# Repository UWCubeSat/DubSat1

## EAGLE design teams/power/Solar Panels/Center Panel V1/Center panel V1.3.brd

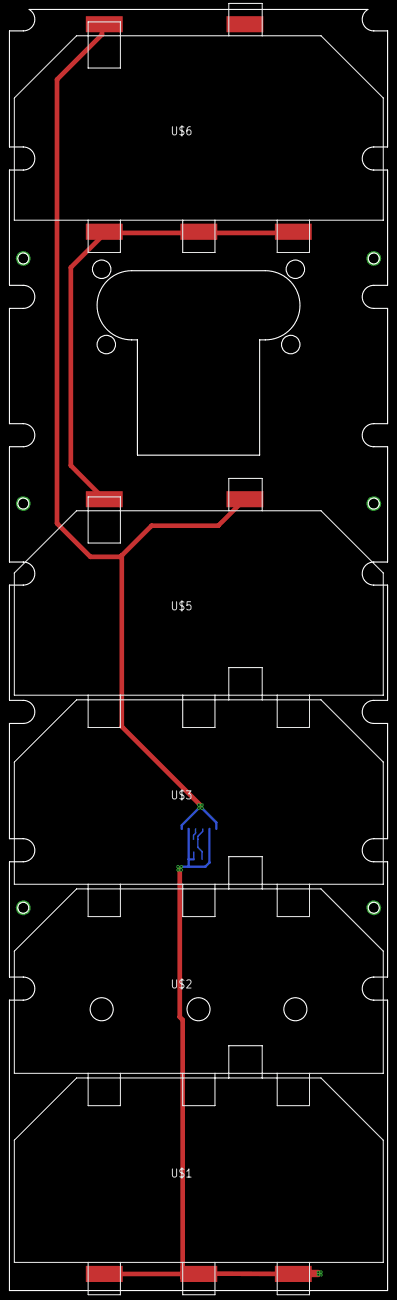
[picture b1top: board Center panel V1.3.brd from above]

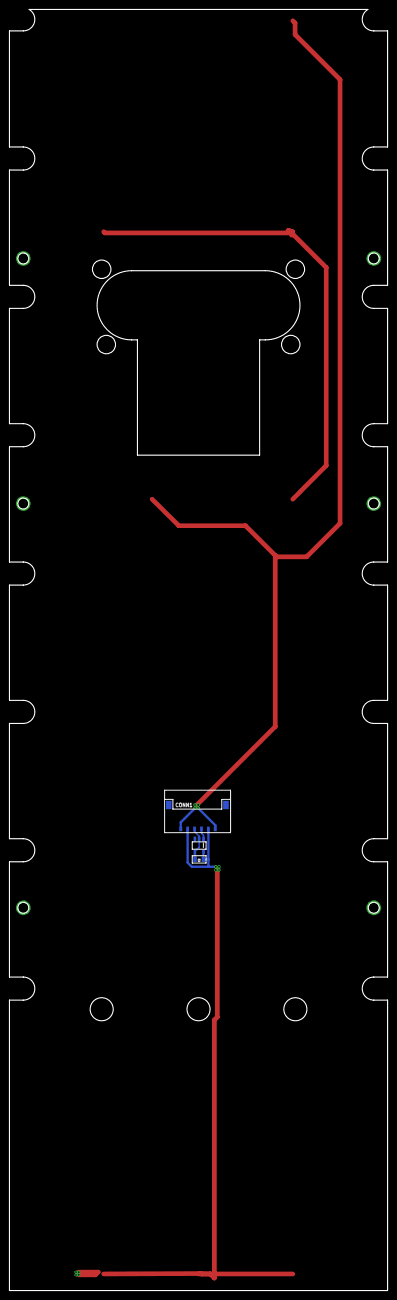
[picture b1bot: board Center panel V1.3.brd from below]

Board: 2 copper layers, 82.0 x 277.8 mm, 8 parts (3 on the bottom side), 5 nets.

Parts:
C2: 0805
CONN1: PICOLOCK_6
U$1: SOLAR_CELL_BOTTOM; SOLAR_CELL_BOTTOM_SHORT-PADS
U$2, U$3: SOALAR_CELL_OUTLINE; SOLAR_CELL_OUTLINE
U$5: SOLAR_CELL_TOP; SOLAR_CELL_TOP_SHORT-PAD
U$6: SOLAR_CELL_STAND-ALONE
U$7: TMP36; SOT-23-5

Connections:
3V3: C2.1, CONN1.P$3, U$7.P$2, U$7.P$4
GND: CONN1.P$2, CONN1.P$5, U$1.P$1, U$1.P$2, U$1.P$3, U$7.P$5
unnamed: U$5.P$2, U$6.P$1, U$6.P$2, U$6.P$3
POWER: CONN1.P$1, CONN1.P$6, U$5.P$1, U$6.P$5
VOUT: CONN1.P$4, U$7.P$1

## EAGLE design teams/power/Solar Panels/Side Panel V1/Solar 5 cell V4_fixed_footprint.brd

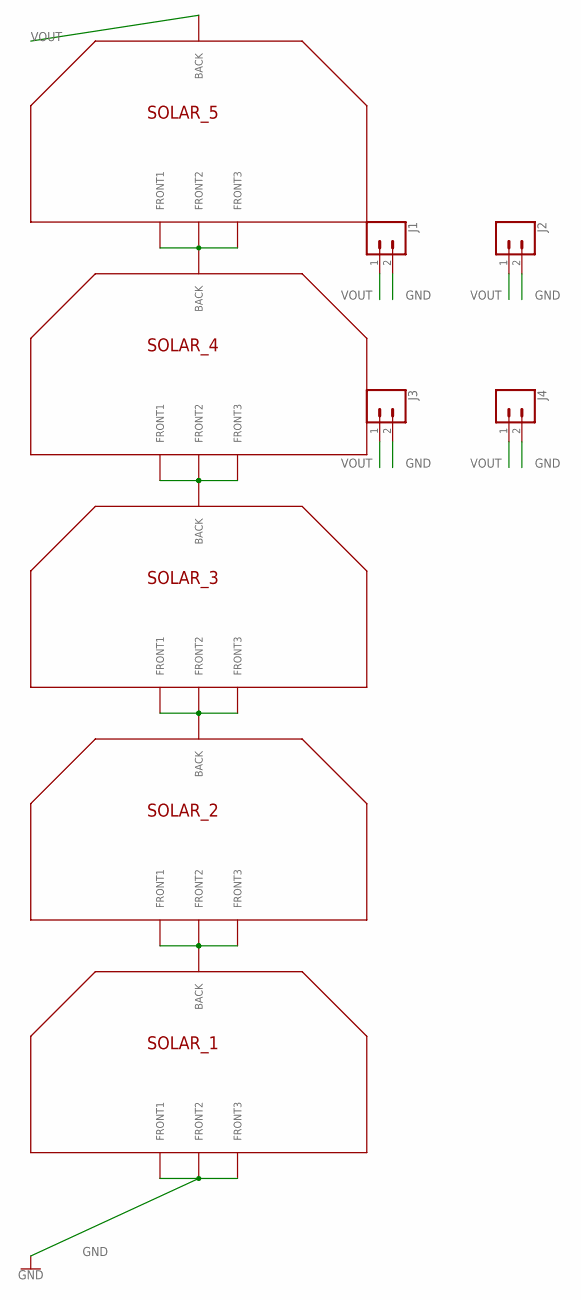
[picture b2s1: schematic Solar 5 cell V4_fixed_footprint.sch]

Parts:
J1, J2, J3, J4: CONN_02; 1X02
SOLAR_1, SOLAR_2, SOLAR_3, SOLAR_4, SOLAR_5: SOLAR_CELL_HALF_TABSFULL_TABS; SOLAR_CELL_3G30A_FULL_TABS

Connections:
1-2: SOLAR_1.P$1 (BACK), SOLAR_2.P$F1 (FRONT1), SOLAR_2.P$F2 (FRONT2), SOLAR_2.P$F3 (FRONT3)
2-3: SOLAR_2.P$1 (BACK), SOLAR_3.P$F1 (FRONT1), SOLAR_3.P$F2 (FRONT2), SOLAR_3.P$F3 (FRONT3)
3-4: SOLAR_3.P$1 (BACK), SOLAR_4.P$F1 (FRONT1), SOLAR_4.P$F2 (FRONT2), SOLAR_4.P$F3 (FRONT3)
4-5: SOLAR_4.P$1 (BACK), SOLAR_5.P$F1 (FRONT1), SOLAR_5.P$F2 (FRONT2), SOLAR_5.P$F3 (FRONT3)
GND: J1.2, J2.2, J3.2, J4.2, SOLAR_1.P$F1 (FRONT1), SOLAR_1.P$F2 (FRONT2), SOLAR_1.P$F3 (FRONT3)
VOUT: J1.1, J2.1, J3.1, J4.1, SOLAR_5.P$1 (BACK)

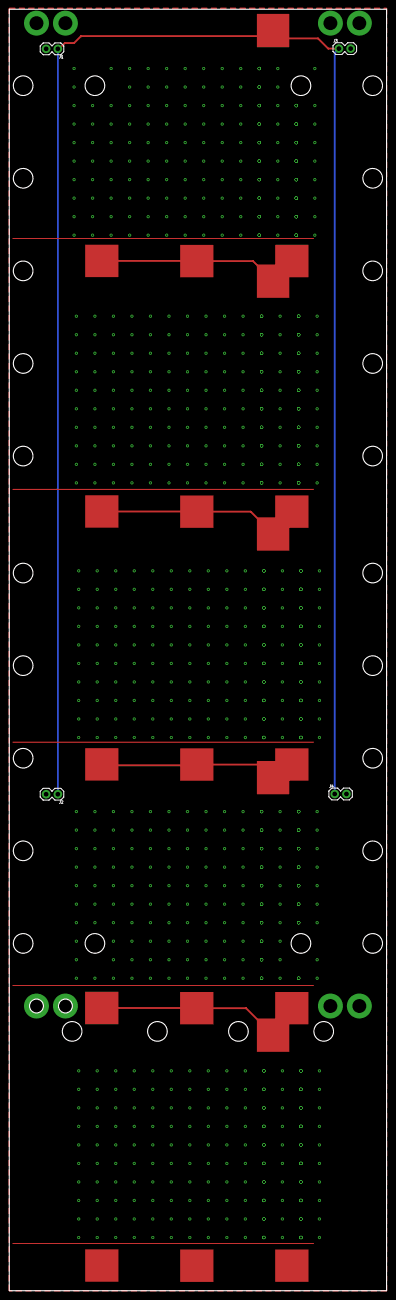
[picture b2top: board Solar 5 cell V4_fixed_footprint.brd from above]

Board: 2 copper layers, 81.5 x 276.8 mm, 9 parts (0 on the bottom side), 6 nets.

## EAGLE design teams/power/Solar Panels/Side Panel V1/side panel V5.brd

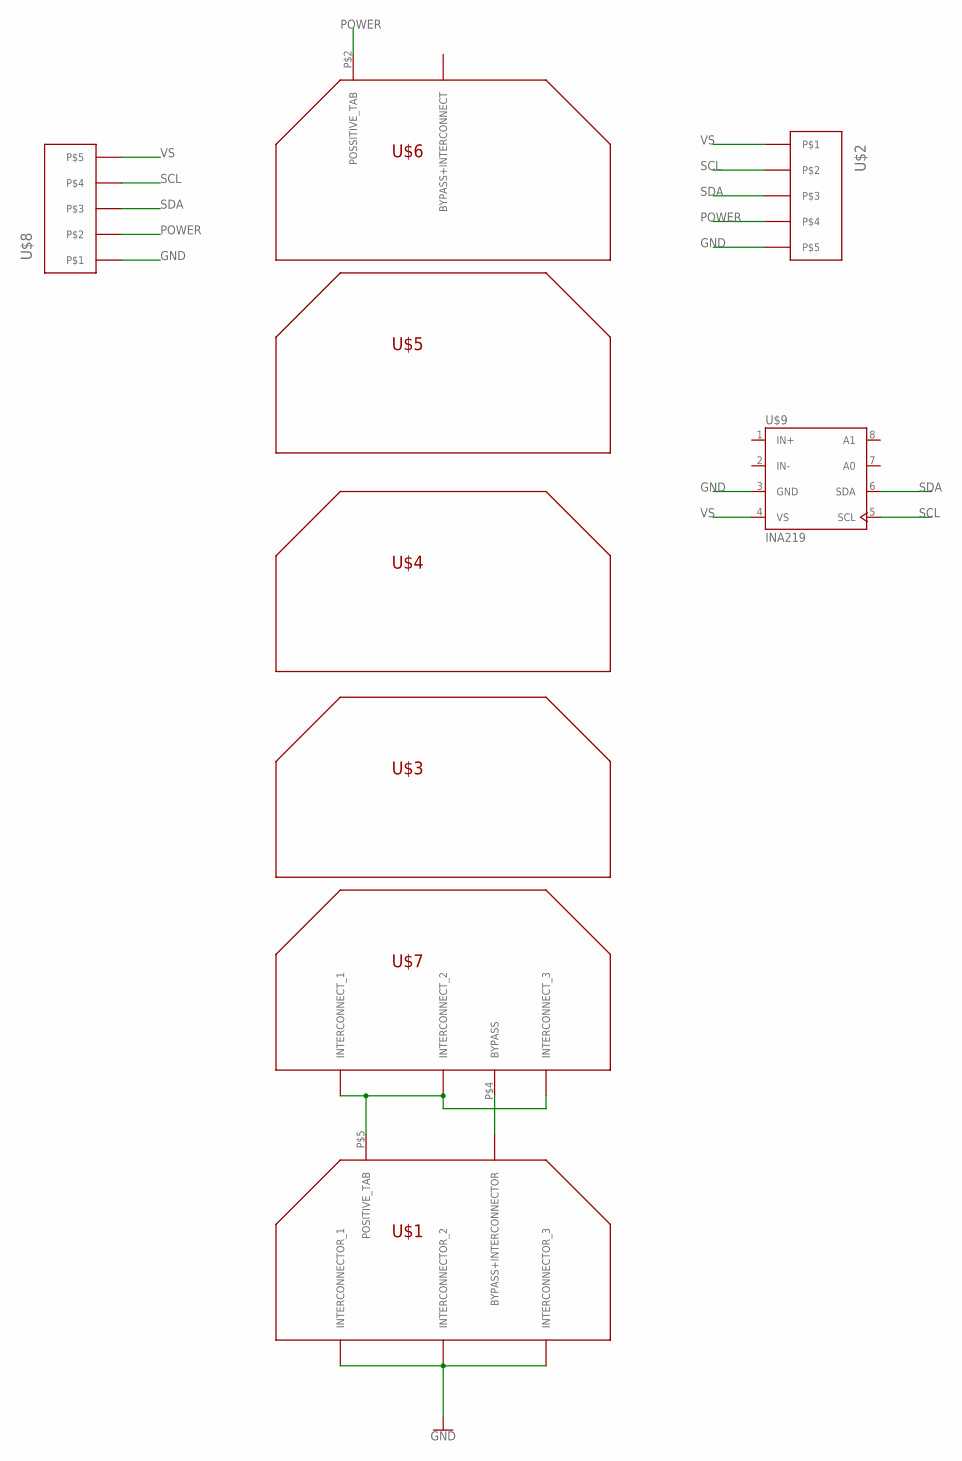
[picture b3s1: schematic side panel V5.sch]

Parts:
U$1: SOLAR_CELL_STAND-ALONE
U$2, U$8: PICOLOCK_5
U$3, U$4, U$5: SOALAR_CELL_OUTLINE; SOLAR_CELL_OUTLINE
U$6: SOLAR_CELL_TOP; SOLAR_CELL_TOP_SHORT-PAD
U$7: SOLAR_CELL_BOTTOM+BYPASS
U$9: INA219; S008

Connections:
GND: U$1.P$1 (INTERCONNECTOR_1), U$1.P$2 (INTERCONNECTOR_2), U$1.P$3 (INTERCONNECTOR_3), U$2.P$5, U$8.P$1, U$9.3 (GND)
unnamed: U$1.P$4 (BYPASS+INTERCONNECTOR), U$7.P$4 (BYPASS)
unnamed: U$1.P$5 (POSITIVE_TAB), U$7.P$1 (INTERCONNECT_1), U$7.P$2 (INTERCONNECT_2), U$7.P$3 (INTERCONNECT_3)
POWER: U$2.P$4, U$6.P$2 (POSSITIVE_TAB), U$8.P$2
SCL: U$2.P$2, U$8.P$4, U$9.5 (SCL)
SDA: U$2.P$3, U$8.P$3, U$9.6 (SDA)
VS: U$2.P$1, U$8.P$5, U$9.4 (VS)

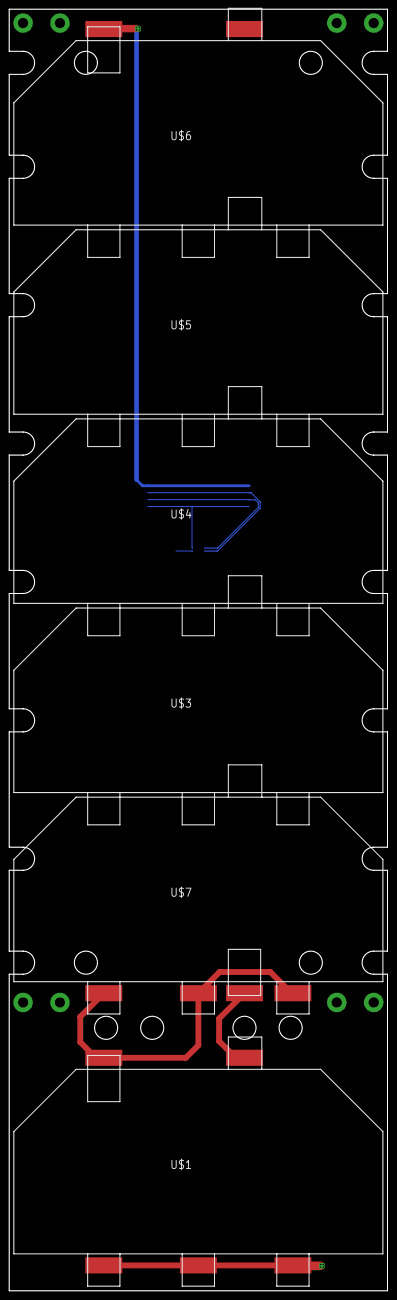
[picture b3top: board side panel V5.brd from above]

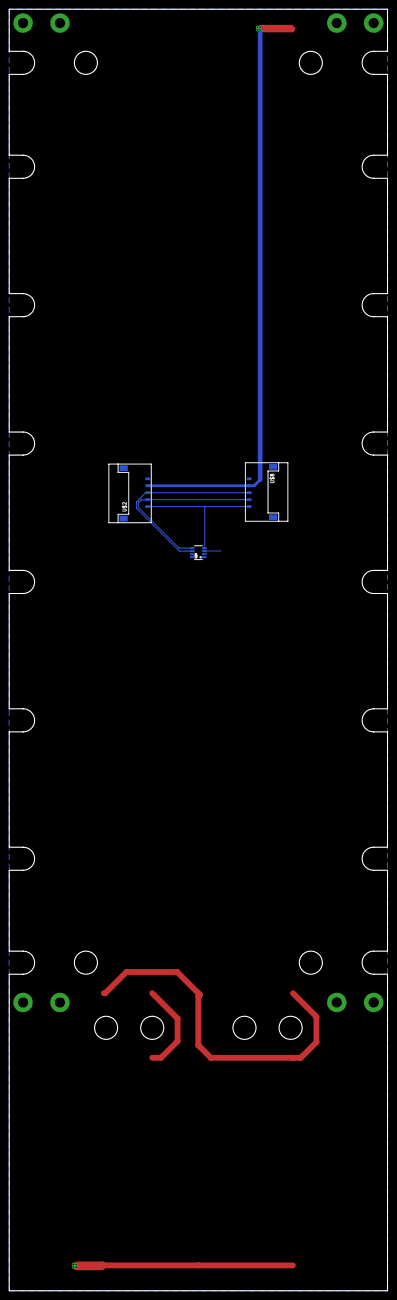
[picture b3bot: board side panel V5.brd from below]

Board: 2 copper layers, 82.0 x 277.8 mm, 9 parts (3 on the bottom side), 7 nets.

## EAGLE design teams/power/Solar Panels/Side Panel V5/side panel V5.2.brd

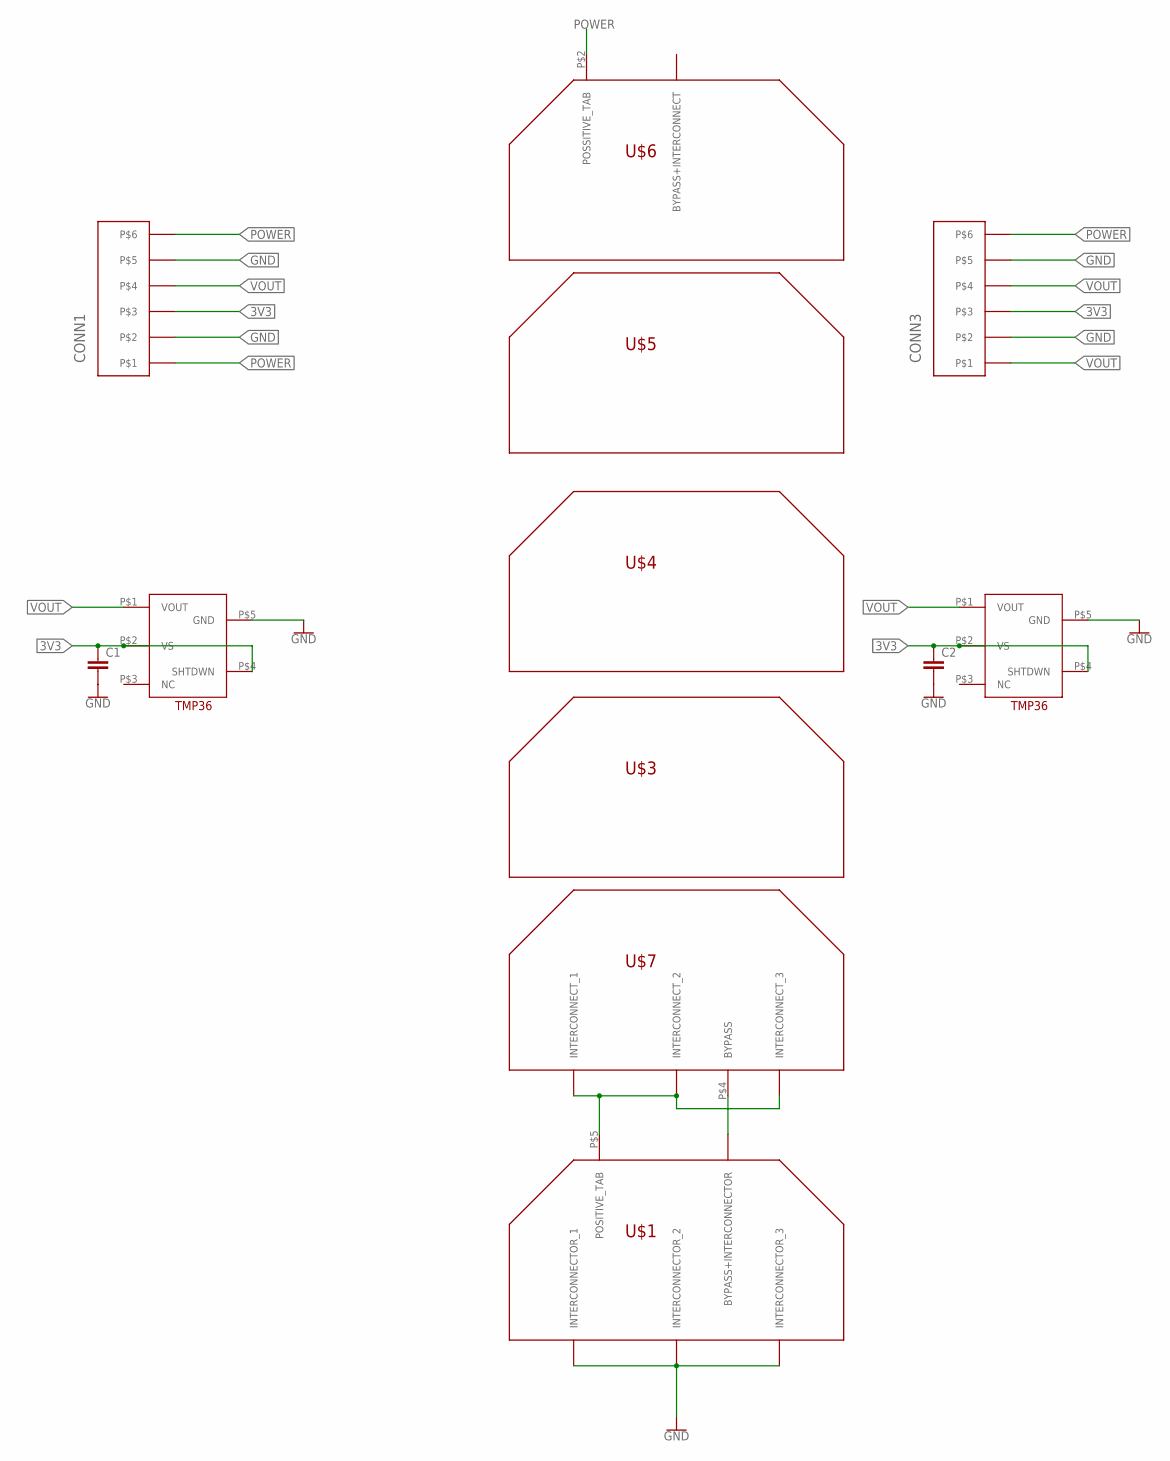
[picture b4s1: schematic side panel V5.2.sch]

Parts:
C1, C2: CAPACITOR0805; 0805
CONN1, CONN3: PICOLOCK_6
U$1: SOLAR_CELL_STAND-ALONE
U$2, U$8: TMP36; SOT-23-5
U$3, U$4, U$5: SOALAR_CELL_OUTLINE; SOLAR_CELL_OUTLINE
U$6: SOLAR_CELL_TOP; SOLAR_CELL_TOP_SHORT-PAD
U$7: SOLAR_CELL_BOTTOM+BYPASS

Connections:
3V3: C1.1, C2.1, CONN1.P$3, CONN3.P$3, U$2.P$2 (VS), U$2.P$4 (SHTDWN), U$8.P$2 (VS), U$8.P$4 (SHTDWN)
GND: C1.2, C2.2, CONN1.P$2, CONN1.P$5, CONN3.P$2, CONN3.P$5, U$1.P$1 (INTERCONNECTOR_1), U$1.P$2 (INTERCONNECTOR_2), U$1.P$3 (INTERCONNECTOR_3), U$2.P$5 (GND), U$8.P$5 (GND)
unnamed: U$1.P$4 (BYPASS+INTERCONNECTOR), U$7.P$4 (BYPASS)
unnamed: U$1.P$5 (POSITIVE_TAB), U$7.P$1 (INTERCONNECT_1), U$7.P$2 (INTERCONNECT_2), U$7.P$3 (INTERCONNECT_3)
POWER: CONN1.P$1, CONN1.P$6, CONN3.P$6, U$6.P$2 (POSSITIVE_TAB)
VOUT: CONN1.P$4, CONN3.P$1, CONN3.P$4, U$2.P$1 (VOUT), U$8.P$1 (VOUT)

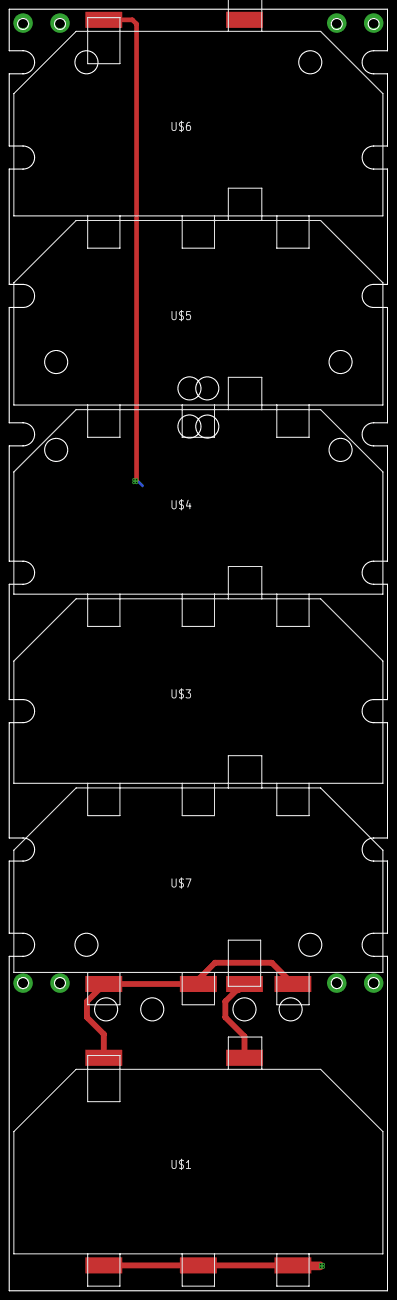
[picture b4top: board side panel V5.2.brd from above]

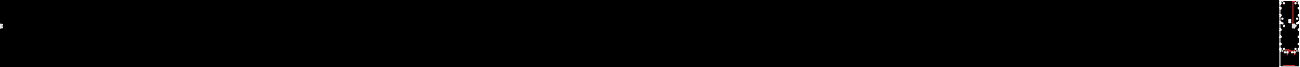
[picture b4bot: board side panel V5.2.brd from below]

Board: 2 copper layers, 82.0 x 277.8 mm, 12 parts (6 on the bottom side), 6 nets.

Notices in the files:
parts and their libraries:
SparkFun-Connectors: Licensing: Creative Commons ShareAlike 4.0 International - https://creativecommons.org/licenses/by-sa/4.0
